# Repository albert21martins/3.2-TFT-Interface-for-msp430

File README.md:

# 3.2-TFT-Interface-for-msp430

Here you can download everything (hard-software) to interface a 3.2" touch TFT to a msp430 launchpad.

You can find more information here:
http://e-homelab.flyvotech.com/index.php/2015/10/08/tft-3-2-interface/

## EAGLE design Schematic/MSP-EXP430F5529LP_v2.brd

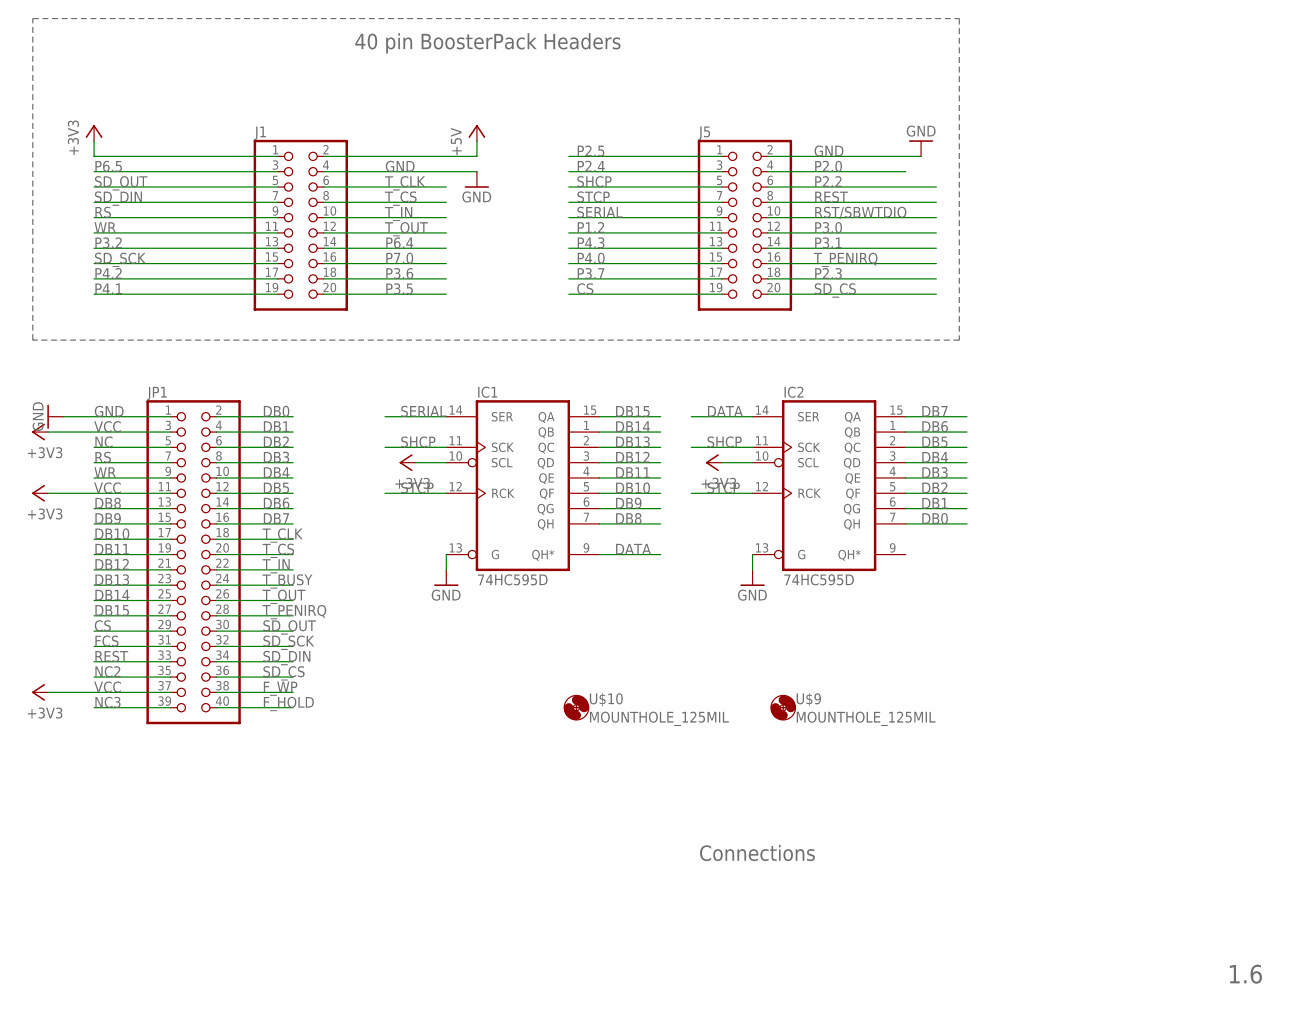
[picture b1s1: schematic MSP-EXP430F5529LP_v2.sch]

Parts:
IC1, IC2: 74HC595D; SO16
J1, J5: PINHD-2X10; 2X10
JP1: PINHD-2X20; 2X20
U$9, U$10: MOUNTHOLE_125MIL

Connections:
+5V: J1.2
CS: J5.19, JP1.29
DATA: IC1.9 (QH*), IC2.14 (SER)
DB0: IC2.7 (QH), JP1.2
DB1: IC2.6 (QG), JP1.4
DB2: IC2.5 (QF), JP1.6
DB3: IC2.4 (QE), JP1.8
DB4: IC2.3 (QD), JP1.10
DB5: IC2.2 (QC), JP1.12
DB6: IC2.1 (QB), JP1.14
DB7: IC2.15 (QA), JP1.16
DB8: IC1.7 (QH), JP1.13
DB9: IC1.6 (QG), JP1.15
DB10: IC1.5 (QF), JP1.17
DB11: IC1.4 (QE), JP1.19
DB12: IC1.3 (QD), JP1.21
DB13: IC1.2 (QC), JP1.23
DB14: IC1.1 (QB), JP1.25
DB15: IC1.15 (QA), JP1.27
FCS: JP1.31
F_HOLD: JP1.40
F_WP: JP1.38
GND: IC1.8 (GND), IC1.13 (G), IC2.8 (GND), IC2.13 (G), J1.4, J5.2, JP1.1
NC: JP1.5
NC2: JP1.35
NC3: JP1.39
P1.2: J5.11
P2.0: J5.4
P2.2: J5.6
P2.3: J5.18
P2.4: J5.3
P2.5: J5.1
P3.0: J5.12
P3.1: J5.14
P3.2: J1.13
P3.5: J1.20
P3.6: J1.18
P3.7: J5.17
P4.0: J5.15
P4.1: J1.19
P4.2: J1.17
P4.3: J5.13
P6.4: J1.14
P6.5: J1.3
P7.0: J1.16
REST: J5.8, JP1.33
RS: J1.9, JP1.7
RST/SBWTDIO: J5.10
SD_CS: J5.20, JP1.36
SD_DIN: J1.7, JP1.34
SD_OUT: J1.5, JP1.30
SD_SCK: J1.15, JP1.32
SERIAL: IC1.14 (SER), J5.9
SHCP: IC1.11 (SCK), IC2.11 (SCK), J5.5
STCP: IC1.12 (RCK), IC2.12 (RCK), J5.7
T_BUSY: JP1.24
T_CLK: J1.6, JP1.18
T_CS: J1.8, JP1.20
T_IN: J1.10, JP1.22
T_OUT: J1.12, JP1.26
T_PENIRQ: J5.16, JP1.28
VCC: IC1.10 (SCL), IC1.16 (VCC), IC2.10 (SCL), IC2.16 (VCC), J1.1, JP1.3, JP1.11, JP1.37
WR: J1.11, JP1.9

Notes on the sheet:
40 pin BoosterPack Headers
Connections
1.6

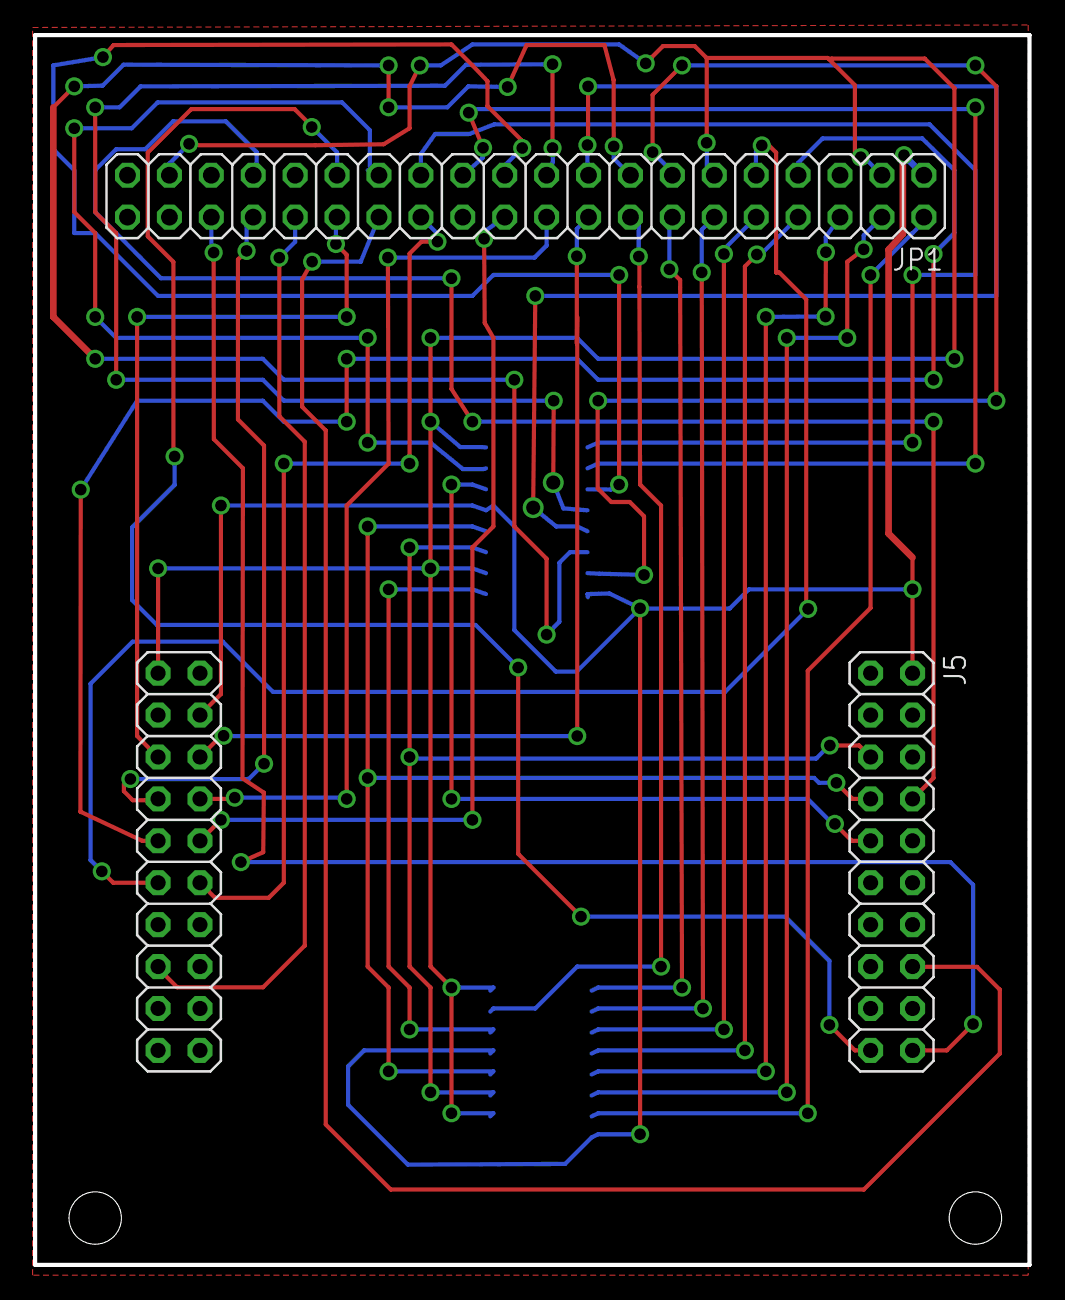
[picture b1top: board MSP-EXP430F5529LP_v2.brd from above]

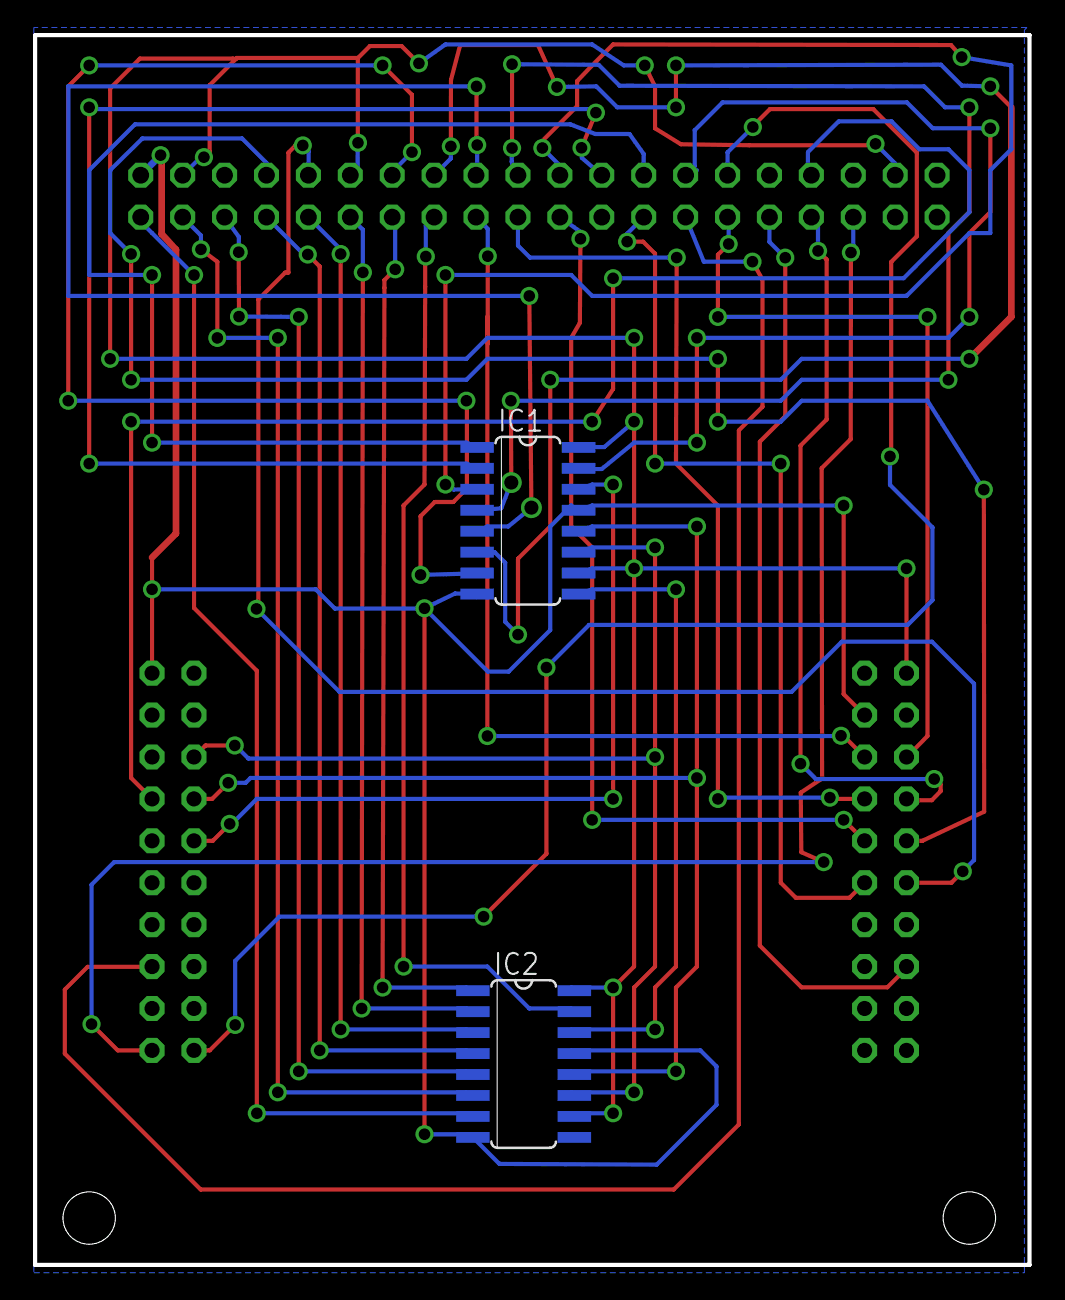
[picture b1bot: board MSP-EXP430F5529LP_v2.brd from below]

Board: 2 copper layers, 60.3 x 74.5 mm, 7 parts (2 on the bottom side), 35 nets.

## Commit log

2015-10-11 tft interface

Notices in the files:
Schematic/MSP-EXP430F5529LP_v2.brd:
(C)2003 A. DANNENBERG
